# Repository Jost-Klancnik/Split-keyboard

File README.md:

# Split Mehanska Tipkovnica

To je repozitorij za razvoj moje lastne "split" ergonomske mehanske tipkovnice, namenjene programrjem, od zasnove do končnega izdelka.

## O Projektu
Gre za razvoj lastne žične "split" tipkovnice, ki bo delovala z dvema Pro Micro krmilnikoma. Polovici bosta med seboj povezani preko TRRS kabla, "master" stran pa bo z računalnikom povezana preko USB-c-ja. Projekt temelji na odprtokodnih orodjih in bo v celoti dokumentiran v tem repozitoriju.

## Načrt Dela
Projekt je razdeljen na več faz, ki si sledijo v logičnem zaporedju. Spodaj je opisan časovni potek in uporabljena orodja.

### Faza 1: Dizajn in Načrtovanje PCB (Zaključeno)
*   **1.1 - Generiranje postavitve (Ergogen):**
    *   **Opis:** Z orodjem [Ergogen](https://ergogen.xyz/) sem na podlagi YAML konfiguracije definiral fizično postavitev tipk, obliko ohišja (plate) in pozicije za vijake.
    *   **Namen:** Ergogen omogoča hitro in parametrično prototipiranje različnih postavitev, kar je bistveno pospešilo iskanje idealne oblike, prav tako pa omogoča enostavno generiranje celotnega vezja, ko smo enkrat zadovoljni s postavitvijo.
    *   **Časovni okvir:** ~8 ur

*   **1.2 - Električni načrt in "Routing" (KiCad):**
    *   **Opis:** Generirane datoteke iz Ergogena sem uvozil v [KiCad](https://www.kicad.org/), kjer sem dokončal električno shemo. To je vključevalo dodajanje Pro Micro krmilnikov, TRRS priključkov, diod (1N4148) in matrike stikal. Nato sem ročno povezal vse komponente ("routing").
    *   **Namen:** KiCad je standard v svetu odprtokodne elektronike in omogoča popoln nadzor nad dizajnom tiskanega vezja (PCB).
    *   **Časovni okvir:** ~10 ur

### Faza 2: Naročilo in Sestavljanje (Naslednji koraki)
*   **2.1 - Izdelava PCB in nabava komponent:**
    *   **Opis:** Iz KiCada bom izvozil Gerber datoteke in jih poslal v izdelavo pri [JLCPCB](https://jlcpcb.com/). Hkrati bom naročil vse potrebne elektronske komponente (stikala, diode, TRRS konektorji, Pro Micro itd.) preko [AliExpressa](https://www.aliexpress.com/).
    *   **Časovni okvir:** ~2-4 tedne (čakanje na dostavo)

*   **2.2 - Spajkanje in montaža:**
    *   **Opis:** Ko prispejo vse komponente, sledi spajkanje diod, TRRS priključkov in Pro Micro krmilnikov na PCB. Na koncu sledi montaža stikal in ohišja.
    *   **Časovni okvir:** trenutno neznan

### Faza 3: Firmware (QMK)
*   **3.1 - Razvoj in konfiguracija:**
    *   **Opis:** Uporabil bom [QMK Firmware](https://qmk.fm/), ki je odprtokodni standard za programsko opremo tipkovnic. Potrebno bo ustvariti novo tipkovnico znotraj QMK, definirati matriko, pine na Pro Micro krmilnikih in nastaviti komunikacijo med obema polovicama.
    *   **Namen:** QMK ponuja izjemno fleksibilnost, podporo za "split" tipkovnice, več plasti (layers), makre in druge napredne funkcije.
    *   **Časovni okvir:** ~10 ur

*   **3.2 - Nalaganje Firmware-a:**
    *   **Opis:** Pripravljen firmware bom s pomočjo QMK Toolboxa ali preko ukazne vrstice naložil ("flashal") na oba Pro Micro krmilnika.

### Faza 4: Prihodnji razvoj
*   **4.1 - Razvoj konfiguracijske aplikacije:**
    *   **Opis:** V prihodnosti načrtujem razvoj lastne aplikacije (verjetno v Pythonu ali z uporabo spletnih tehnologij), ki bi omogočala spreminjanje postavitve tipk (keymap) v realnem času, brez potrebe po ponovnem nalaganju celotnega firmware-a.

## Infrastruktura in Namestitev

Za razvoj projekta so potrebna določena orodja. Spodaj so navodila za namestitev na različnih operacijskih sistemih.

### Osnovne predpogoji
Pred namestitvijo specifičnih orodij se prepričajte, da imate na sistemu nameščene:
*   **Git:** Za upravljanje z repozitorijem.
*   **Python (verzija 3.8 ali novejša) in Pip:** Potrebno za QMK.
*   **Node.js in NPM:** Potrebno za Ergogen.

---

### Namestitev na Arch Linux
*   **Vsa orodja (All-in-one):**
    ```bash
    # Git, Python, Pip, NodeJS, NPM in osnovna orodja za gradnjo
    sudo pacman -S git python-pip nodejs npm base-devel

    # KiCad
    sudo pacman -S kicad kicad-library kicad-library-3d
    ```
*   **Specifična orodja (po korakih):**
    ```bash
    # Ergogen
    npm install -g ergogen

    # QMK CLI
    pip install qmk
    qmk setup # Sledi navodilom za namestitev odvisnosti
    ```

---

### Namestitev na Windows
*   **Osnovna orodja:**
    *   **Git:** Prenesite in namestite [Git for Windows](https://git-scm.com/download/win).
    *   **Python:** Prenesite in namestite s [python.org](https://www.python.org/downloads/). 
    *   **Node.js:** Prenesite in namestite z [nodejs.org](https://nodejs.org/en/download/).
*   **Specifična orodja:**
    *   **KiCad:** Prenesite in namestite z [uradne strani KiCad](https://www.kicad.org/download/).
    *   **Ergogen & QMK:** Zaženite **Command Prompt** ali **PowerShell** in vpišite ukaze:
        ```powershell
        # Ergogen (preko NPM)
        npm install -g ergogen

        # QMK (preko Pip)
        pip install qmk
        qmk setup
        ```

---

### Namestitev na macOS
*   **Osnovna orodja (preko Homebrew):**
    *   Najprej namestite [Homebrew](https://brew.sh/), če ga še nimate.
    ```bash
    # Git, Python in Node.js
    brew install git python node
    ```
*   **Specifična orodja:**
    *   **KiCad:**
        ```bash
        brew install --cask kicad
        ```
    *   **Ergogen & QMK:**
        ```bash
        # Ergogen (preko NPM)
        npm install -g ergogen

        # QMK (preko Pip)
        pip3 install qmk # Uporabite pip3, da se izognete konfliktu s sistemskim Pythonom
        qmk setup # Sledi navodilom v terminalu
        ```

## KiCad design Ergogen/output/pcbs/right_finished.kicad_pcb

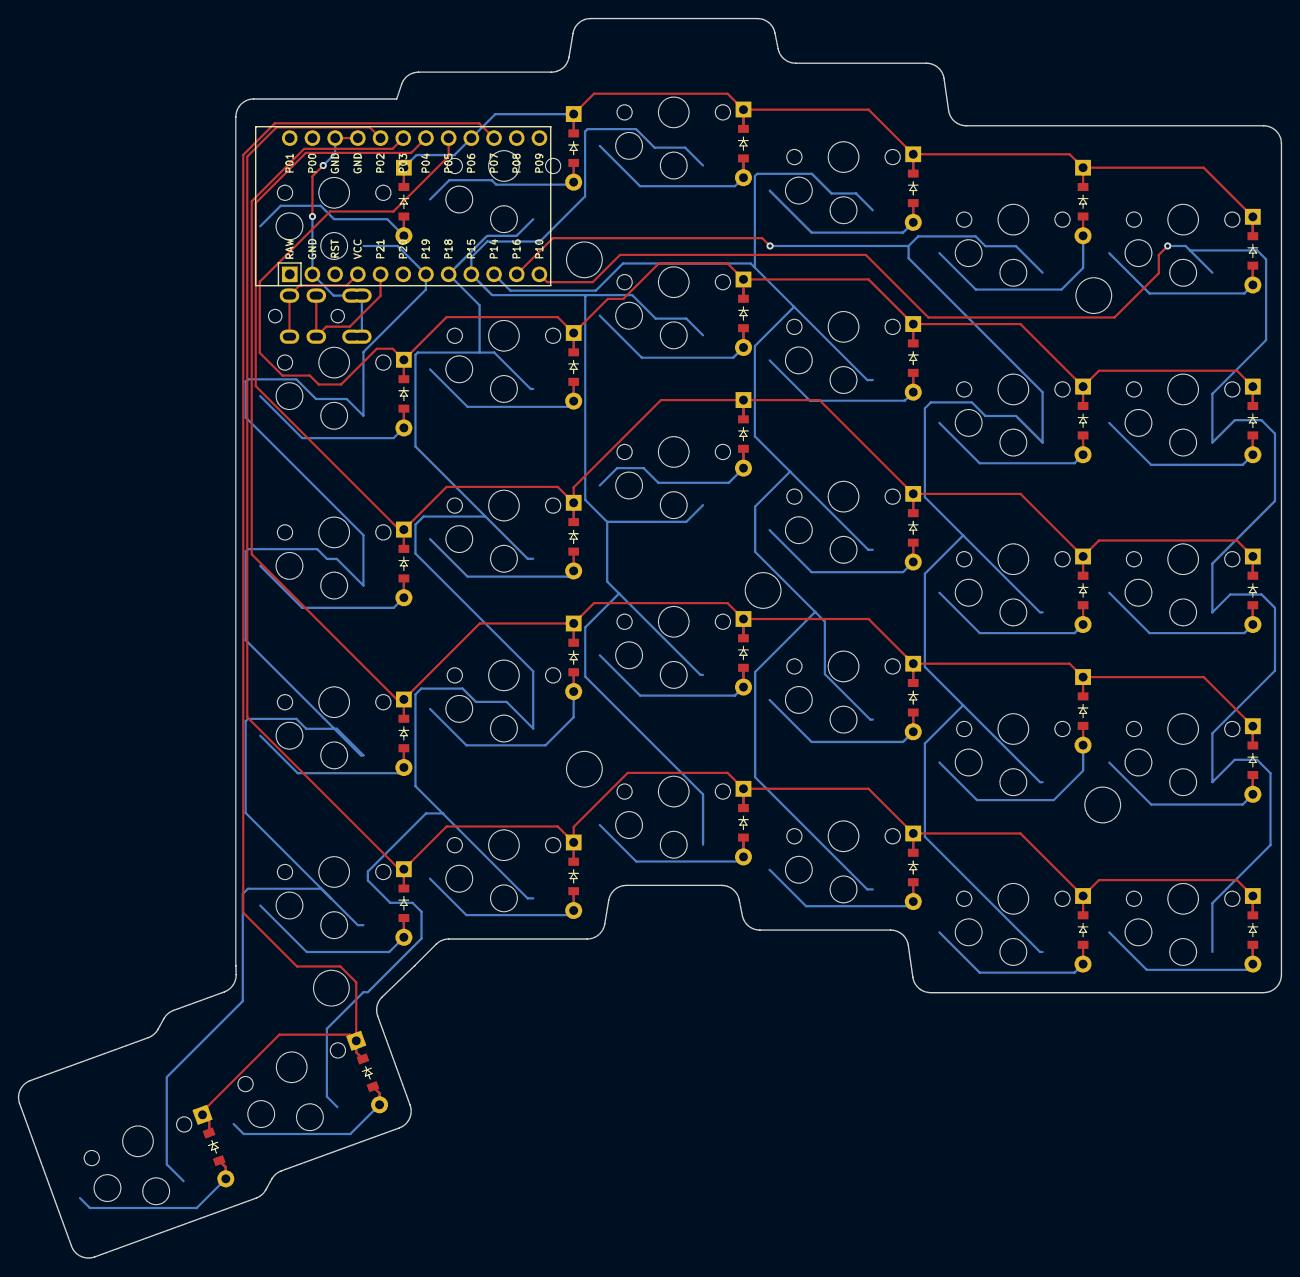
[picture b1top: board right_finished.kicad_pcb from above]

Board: 2 copper layers, 141.3 x 138.7 mm, 66 parts (0 on the bottom side), 47 nets.

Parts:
D1, D2, D3, D4, D5, D6, D7, D8, D9, D10, D11, D12, D13, D14, D15, D16, D17, D18, D19, D20, D21, D22, D23, D24, D25, D26, D27, D28, D29, D30, D31, D32: ComboDiode
MCU1: ProMicro
S1, S2, S3, S4, S5, S6, S7, S8, S9, S10, S11, S12, S13, S14, S15, S16, S17, S18, S19, S20, S21, S22, S23, S24, S25, S26, S27, S28, S29, S30, S31, S32: PG1350
TRRS1: TRRS-PJ-320A-dual

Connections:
GND: MCU1.2, MCU1.15, MCU1.16, TRRS1.1, TRRS1.2
P2: D1.1, D6.1, D9.1, D14.1, D18.1, D21.1, MCU1.17
P3: D2.1, D10.1, D15.1, D22.1, D25.1, D28.1, MCU1.18
P4: D3.1, D7.1, D11.1, D19.1, D23.1, D27.1, MCU1.19
P5: D4.1, D8.1, D12.1, D16.1, D20.1, D24.1, MCU1.20
P6: D5.1, D13.1, D17.1, D26.1, D29.1, D30.1, MCU1.21
P7: D31.1, D32.1, MCU1.22
P10: MCU1.12, S1.1, S2.1, S3.1, S4.1, S5.1
P14: MCU1.10, S11.1, S12.1, S13.1, S14.1, S15.1
P15: MCU1.9, S16.1, S17.1, S18.1, S19.1, S20.1
P16: MCU1.11, S6.1, S7.1, S8.1, S9.1, S10.1
P18: MCU1.8, S21.1, S22.1, S23.1, S24.1, S25.1, S31.1
P19: MCU1.7, S26.1, S27.1, S28.1, S29.1, S30.1, S32.1
P21: MCU1.5, TRRS1.3
VCC: MCU1.4, TRRS1.4
mirror_fifth_bottom: D28.2, S22.2
mirror_fifth_home: D19.2, S23.2
mirror_fifth_mod: D18.2, S21.2
mirror_fifth_num: D29.2, S25.2
mirror_fifth_top: D20.2, S24.2
mirror_first_bottom: D2.2, S2.2
mirror_first_home: D3.2, S3.2
mirror_first_mod: D1.2, S1.2
mirror_first_num: D5.2, S5.2
mirror_first_top: D4.2, S4.2
mirror_fourth_bottom: D15.2, S17.2
mirror_fourth_home: D27.2, S18.2
mirror_fourth_mod: D14.2, S16.2
mirror_fourth_num: D17.2, S20.2
mirror_fourth_top: D16.2, S19.2
mirror_second_bottom: D25.2, S7.2
mirror_second_home: D7.2, S8.2
mirror_second_mod: D6.2, S6.2
mirror_second_num: D26.2, S10.2
mirror_second_top: D8.2, S9.2
mirror_sixth_bottom: D22.2, S27.2
mirror_sixth_home: D23.2, S28.2
mirror_sixth_mod: D21.2, S26.2
mirror_sixth_num: D30.2, S30.2
mirror_sixth_top: D24.2, S29.2
mirror_t1_thumb: D31.2, S31.2
mirror_t2_thumb: D32.2, S32.2
mirror_third_bottom: D10.2, S12.2
mirror_third_home: D11.2, S13.2
mirror_third_mod: D9.2, S11.2
mirror_third_num: D13.2, S15.2
mirror_third_top: D12.2, S14.2

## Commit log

2025-10-26 Initial commit (added ergogen files)
2025-10-26 Added README.md
2025-11-23 Revise README with project overview and setup instructions
    Updated README to include project details in Slovenian, added phases of development, and installation instructions for various operating systems.
2026-02-09 Updated Ergogen files
2026-02-09 Added Firmware.
2026-02-09 Added .STL files for keyboard case.
2026-02-09 Updated /Firmware file hierarchy.
2026-02-10 Started to work on a new keymap
2026-02-10 Made ščž work.
2026-02-11 Updated Ergogen config.yaml for case fixes
2026-02-11 Changed keyholes scale from 14 to 14.5
2026-02-11 Made standoffs xs 0.1 bigger for 3D printing.
2026-02-16 Updated keymap v1.
